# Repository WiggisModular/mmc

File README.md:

# modular modular case 

## Hackaday.io project

https://hackaday.io/project/174341-modular-modular-case

## Repo organisation

### psu
Subdirectories for different powersupplies, only eurorack 1A right now.

### openscad
openscad files

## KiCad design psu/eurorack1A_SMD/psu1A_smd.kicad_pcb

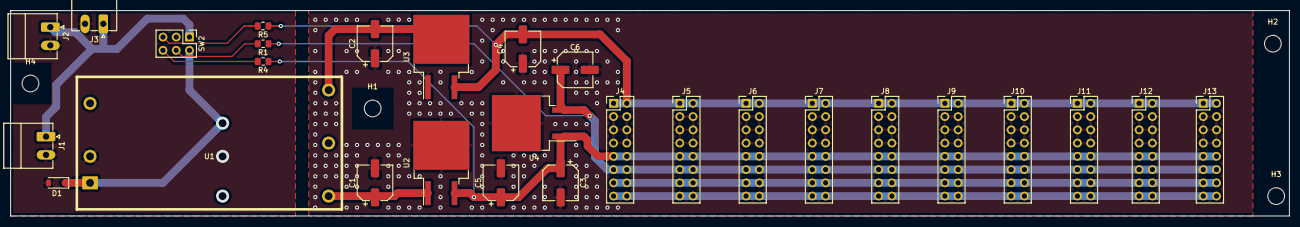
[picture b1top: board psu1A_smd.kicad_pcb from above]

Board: 2 copper layers, 245.1 x 39.4 mm, 32 parts (0 on the bottom side), 14 nets.

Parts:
C1, C2, C3, C4, C5, C6: 330n; CP_Elec_6.3x4.9
D1: 1N5406RLG; D_SOD-123
H1, H2, H3, H4: MountingHole; MountingHole_3.2mm_M3
J1, J2, J3: Conn_01x02_Male; PhoenixContact_MC_1,5_2-G-3.5_1x02_P3.50mm_Horizontal
J4, J5, J6, J7, J8, J9, J10, J11, J12, J13: Conn_02x08_Odd_Even; PinHeader_2x08_P2.54mm_Vertical
R1, R4, R5: R; R_0805_2012Metric_Pad1.15x1.40mm_HandSolder
SW2: Conn_02x03_Odd_Even; PinHeader_2x03_P2.54mm_Vertical
U1: PYBE30-Q24-D15; PYBE30
U2: LM7812_TO220; TO-263-2
U3: LM7912_TO220; TO-263-2
U4: LM7805_TO220; TO-263-2

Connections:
0V: C1.2, C2.1, C3.2, C4.1, C5.2, C6.2, J4.3, J4.4, J4.5, J4.6, J4.7, J4.8, J5.3, J5.4, J5.5, J5.6, J5.7, J5.8, J6.3, J6.4, J6.5, J6.6, J6.7, J6.8, J7.3, J7.4, J7.5, J7.6, J7.7, J7.8, J8.3, J8.4, J8.5, J8.6, J8.7, J8.8, J9.3, J9.4, J9.5, J9.6, J9.7, J9.8, J10.3, J10.4, J10.5, J10.6, J10.7, J10.8, J11.3, J11.4, J11.5, J11.6, J11.7, J11.8, J12.3, J12.4, J12.5, J12.6, J12.7, J12.8, J13.3, J13.4, J13.5, J13.6, J13.7, J13.8, SW2.3, U2.2, U3.1, U4.2
+5V: C6.1, J4.11, J4.12, J5.11, J5.12, J6.11, J6.12, J7.11, J7.12, J8.11, J8.12, J9.11, J9.12, J10.11, J10.12, J11.11, J11.12, J12.11, J12.12, J13.11, J13.12, R1.1, U4.3
+12V: C3.1, C5.1, J4.9, J4.10, J5.9, J5.10, J6.9, J6.10, J7.9, J7.10, J8.9, J8.10, J9.9, J9.10, J10.9, J10.10, J11.9, J11.10, J12.9, J12.10, J13.9, J13.10, R4.1, U2.3, U4.1
+15V: C1.1, U1.6, U2.1
-12V: C4.2, J4.1, J4.2, J5.1, J5.2, J6.1, J6.2, J7.1, J7.2, J8.1, J8.2, J9.1, J9.2, J10.1, J10.2, J11.1, J11.2, J12.1, J12.2, J13.1, J13.2, R5.1, U3.3
-15V: C2.2, U1.4, U3.2
CV: J4.13, J4.14, J5.13, J5.14, J6.13, J6.14, J7.13, J7.14, J8.13, J8.14, J9.13, J9.14, J10.13, J10.14, J11.13, J11.14, J12.13, J12.14, J13.13, J13.14
GND: D1.2, J1.2, J2.2, J3.2, U1.2
Gate: J4.15, J4.16, J5.15, J5.16, J6.15, J6.16, J7.15, J7.16, J8.15, J8.16, J9.15, J9.16, J10.15, J10.16, J11.15, J11.16, J12.15, J12.16, J13.15, J13.16
unnamed: J1.1, J2.1, J3.1, SW2.1
unnamed: R1.2, SW2.4
unnamed: R4.2, SW2.6
unnamed: R5.2, SW2.5
VIN: D1.1, SW2.2, U1.1

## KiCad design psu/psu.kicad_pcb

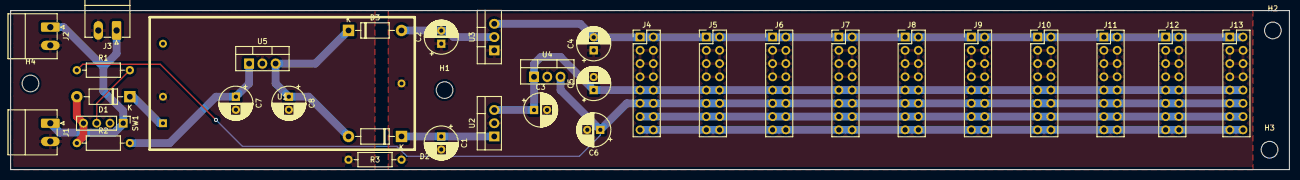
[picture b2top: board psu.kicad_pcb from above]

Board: 2 copper layers, 245.1 x 30.5 mm, 37 parts (0 on the bottom side), 15 nets.

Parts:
C1, C2, C3, C4, C5, C6: 330n; CP_Radial_D6.3mm_P2.50mm
C7, C8: 22u/50V; CP_Radial_D6.3mm_P2.50mm
D1, D2, D3: 1N5406RLG; D_DO-41_SOD81_P10.16mm_Horizontal
H1, H2, H3, H4: MountingHole; MountingHole_3.2mm_M3
J1, J2, J3: Conn_01x02_Male; PhoenixContact_MC_1,5_2-G-3.5_1x02_P3.50mm_Horizontal
J4, J5, J6, J7, J8, J9, J10, J11, J12, J13: Conn_02x08_Odd_Even; PinHeader_2x08_P2.54mm_Vertical
R1: R; R_Axial_DIN0207_L6.3mm_D2.5mm_P10.16mm_Horizontal
R2, R3: 0R; R_Axial_DIN0207_L6.3mm_D2.5mm_P10.16mm_Horizontal
SW1: SW_MEC_5G_LED; PinHeader_1x04_P2.54mm_Vertical
U1: PYBE30-Q24-D15; PYBE30
U2: LM7812_TO220; TO-220-3_Vertical
U3: LM7912_TO220; TO-220-3_Vertical
U4: LM7805_TO220; TO-220-3_Vertical
U5: VR20S12; TO-220-3_Vertical

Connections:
0V: C1.2, C2.1, C3.2, C4.1, C5.2, C6.2, J4.3, J4.4, J4.5, J4.6, J4.7, J4.8, J5.3, J5.4, J5.5, J5.6, J5.7, J5.8, J6.3, J6.4, J6.5, J6.6, J6.7, J6.8, J7.3, J7.4, J7.5, J7.6, J7.7, J7.8, J8.3, J8.4, J8.5, J8.6, J8.7, J8.8, J9.3, J9.4, J9.5, J9.6, J9.7, J9.8, J10.3, J10.4, J10.5, J10.6, J10.7, J10.8, J11.3, J11.4, J11.5, J11.6, J11.7, J11.8, J12.3, J12.4, J12.5, J12.6, J12.7, J12.8, J13.3, J13.4, J13.5, J13.6, J13.7, J13.8, R3.2, U1.5, U2.2, U3.1, U4.2
+5V: C6.1, J4.11, J4.12, J5.11, J5.12, J6.11, J6.12, J7.11, J7.12, J8.11, J8.12, J9.11, J9.12, J10.11, J10.12, J11.11, J11.12, J12.11, J12.12, J13.11, J13.12, R1.1, U4.3
+12V: C3.1, C5.1, J4.9, J4.10, J5.9, J5.10, J6.9, J6.10, J7.9, J7.10, J8.9, J8.10, J9.9, J9.10, J10.9, J10.10, J11.9, J11.10, J12.9, J12.10, J13.9, J13.10, U2.3, U4.1
+15V: C1.1, D2.1, U1.6, U2.1
-12V: C4.2, J4.1, J4.2, J5.1, J5.2, J6.1, J6.2, J7.1, J7.2, J8.1, J8.2, J9.1, J9.2, J10.1, J10.2, J11.1, J11.2, J12.1, J12.2, J13.1, J13.2, U3.3
-15V: C2.2, D3.2, U1.4, U3.2
CV: J4.13, J4.14, J5.13, J5.14, J6.13, J6.14, J7.13, J7.14, J8.13, J8.14, J9.13, J9.14, J10.13, J10.14, J11.13, J11.14, J12.13, J12.14, J13.13, J13.14
GND: C7.2, C8.2, J1.2, J2.2, J3.2, R3.1, SW1.2, U1.2, U5.2
Gate: J4.15, J4.16, J5.15, J5.16, J6.15, J6.16, J7.15, J7.16, J8.15, J8.16, J9.15, J9.16, J10.15, J10.16, J11.15, J11.16, J12.15, J12.16, J13.15, J13.16
unnamed: C7.1, R2.2, U5.1
unnamed: C8.1, D2.2, D3.1, U5.3
unnamed: D1.1, U1.1
unnamed: J1.1, J2.1, J3.1, SW1.1
unnamed: R1.2, SW1.3
VIN: D1.2, R2.1, SW1.4

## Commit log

2020-09-09 reorganised kicad
2020-09-09 added gitignore
2020-09-09 moved gitignore to openscad
2020-09-13 Renamed and made 4U
2020-09-13 moved hole
2020-09-13 moved holes to 4U.scad
2020-09-13 Added schematic pdf
2020-09-13 Split the BOM into variants, added order no
2020-09-13 Preparations for next revision
2020-09-16 simplified configuration
2020-09-22 fixed height
2020-09-22 dxf generated
2020-09-22 lightburn and g-code to gitignore
2020-10-05 dropped option 1
2020-10-05 added DKMW30
2020-10-06 SMD version added
2020-10-07 SMD done
2021-03-20 V2 base
